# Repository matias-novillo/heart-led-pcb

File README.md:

# Heart LED Board

A heart-shaped PCB with 12 red LEDs around the edge. Press the button and the LEDs light up one after the other around the heart, then all of them light for a second at the end. Runs off a CR2032 coin cell and sleeps between presses.

Designed in KiCad, fabricated by JLCPCB, hand soldered.

## Status

- [x] Schematic
- [x] PCB layout (DRC, ERC and schematic parity clean)
- [x] Boards and parts ordered
- [ ] Assembly
- [ ] Firmware
- [ ] Tested

## Specs

| | |
|---|---|
| Board | 70 × 63 mm, 2-layer FR-4, 1.6 mm |
| MCU | STM32G031F6P6 (Cortex-M0+, TSSOP-20) |
| LEDs | 12 × red 1206 (LTST-C150KRKT), 220 Ω each, about 4.5 mA |
| Power | CR2032 coin cell, no regulator |
| Input | One tactile button on PC15 (internal pull-up, wakes the MCU) |
| Programming | 5-pin SWD header (3V3, SWDIO, SWCLK, NRST, GND) |

## How it works

Each LED has its own GPIO pin and resistor, so the MCU can light any LED directly. Only one LED is on at a time during the chase, which keeps the load on the coin cell to about 6.5 mA.

Lighting all 12 at once would pull about 54 mA, which a CR2032 can't supply without the voltage sagging and the MCU browning out. For the "all on" finale, the firmware multiplexes: it cycles through small groups of LEDs fast enough that they all look lit, while the battery only ever sees a few LEDs' worth of current.

Between presses the MCU sits in Stop mode at a few µA. The button wakes it through an EXTI interrupt.

## Pin map

| Signal | MCU pin | Pin # |
|---|---|---|
| LED1–LED8 | PA0–PA7 | 7–14 |
| LED9 | PA8/PB0/PB1/PB2 | 15 |
| LED10 | PA9/PA11 | 16 |
| LED11 | PA10/PA12 | 17 |
| LED12 | PB7/PB8 | 1 |
| Button | PC15 | 3 |
| SWDIO | PA13 | 18 |
| SWCLK | PA14 | 19 |
| NRST | PF2-NRST | 6 |

Pins 1, 15, 16 and 17 have several GPIOs bonded to one physical pin. Only one GPIO per pin should be configured as an output; the rest stay in analog mode.

## Repository layout

```
hardware/      KiCad project (schematic, PCB, project file)
fab/           Gerbers and drill files sent to JLCPCB
docs/          Schematic PDF and BOM
images/        Renders and photos
firmware/      STM32CubeIDE project (coming soon)
```

## Bill of materials

| Ref | Qty | Part | Manufacturer part # |
|---|---|---|---|
| U1 | 1 | STM32G031F6P6 | STM32G031F6P6 |
| D1–D12 | 12 | Red LED, 1206 | LTST-C150KRKT |
| R1–R12 | 12 | 220 Ω, 1206 | RC1206FR-07220RL |
| C1, C3 | 2 | 100 nF, 0805 | CL21B104KBCNNNC |
| C2 | 1 | 4.7 µF, 0805 | CL21A475KAQNNNE |
| SW1 | 1 | 6 mm tactile switch | B3F-1000 |
| BT1 | 1 | CR2032 holder | Keystone 3034 |
| J1 | 1 | 1×5 2.54 mm header | PRPC040SAAN-RC (cut to 5) |

## Programming

The board is flashed over SWD using the ST-Link built into a NUCLEO-G071RB. Remove the two CN4 jumpers on the Nucleo, then wire its CN11 header to J1:

| Nucleo CN11 | J1 |
|---|---|
| 1 VDD_TARGET | 1 3V3 |
| 2 SWCLK | 3 SWCLK |
| 3 GND | 5 GND |
| 4 SWDIO | 2 SWDIO |
| 5 NRST | 4 NRST (optional, needs SB19 opened on the Nucleo) |

The heart runs on its own coin cell while programming. VDD_TARGET only senses the target voltage.

## What I'd change in a rev 2

- More even LED spacing around the outline (the gaps currently range from about 7 mm to 19 mm; the firmware compensates by scaling the step delay to each gap)
- A ground pour on the back layer
- Decoupling caps closer to the VDD pin

## License

Hardware: [CERN-OHL-P v2](https://ohwr.org/cern_ohl_p_v2.txt)
Firmware: MIT

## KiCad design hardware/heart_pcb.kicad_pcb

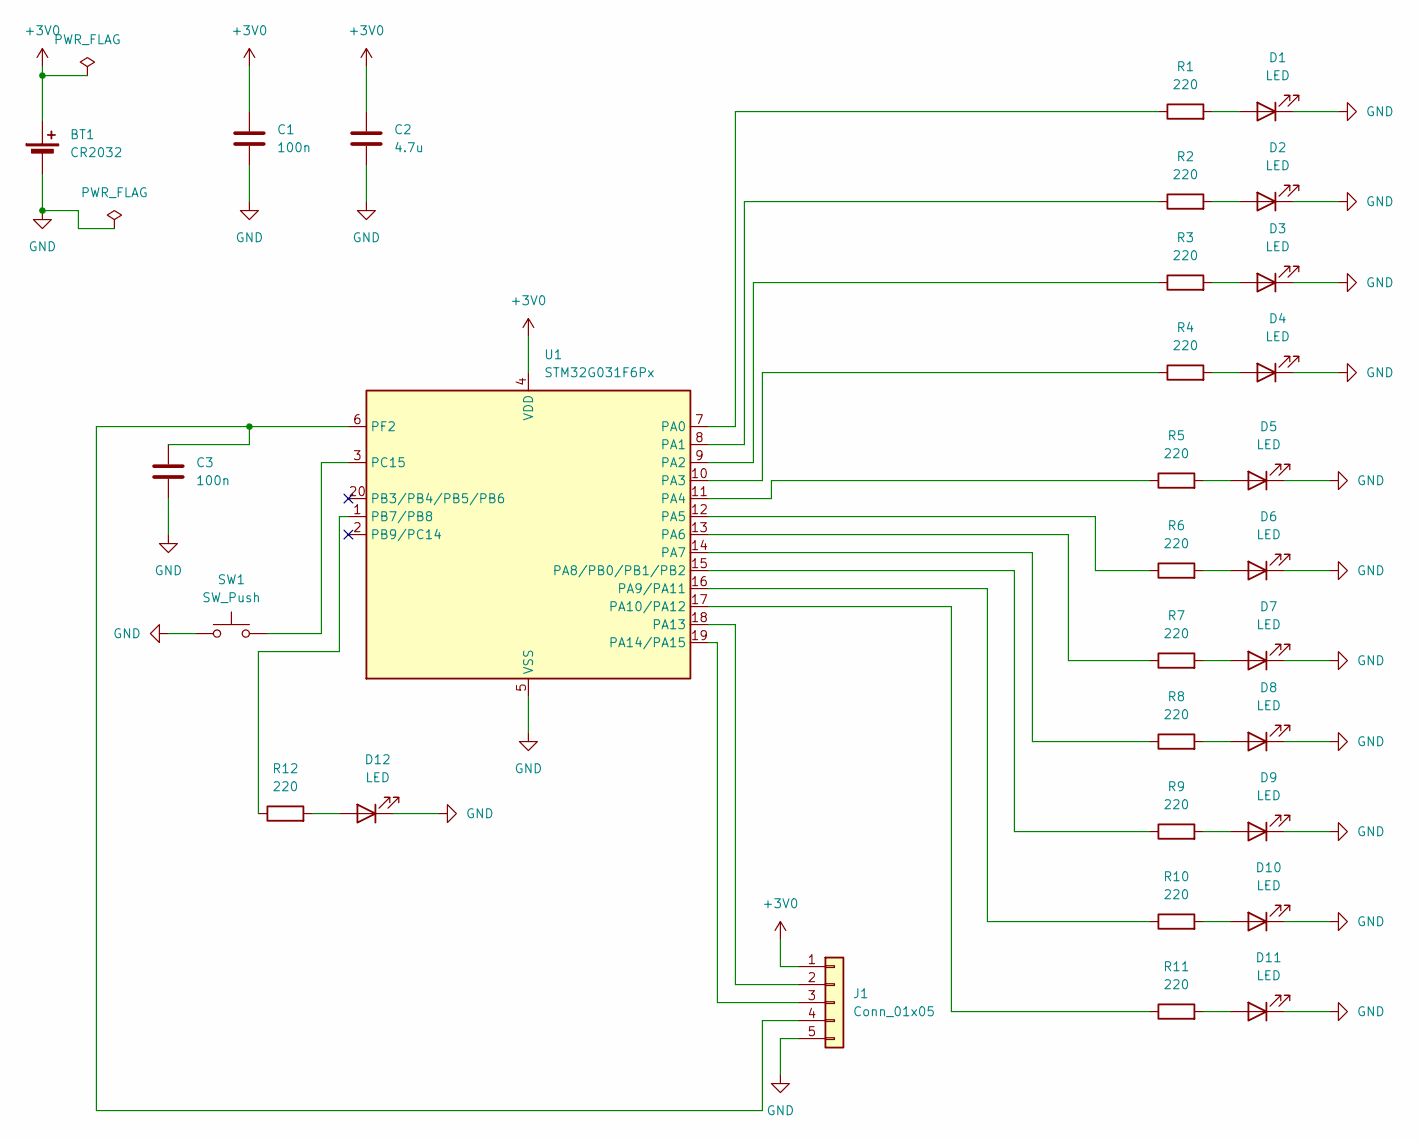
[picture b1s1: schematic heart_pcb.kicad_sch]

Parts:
BT1: CR2032; BatteryHolder_Keystone_3034_1x20mm
C1, C3: 100n; C_0805_2012Metric_Pad1.18x1.45mm_HandSolder
C2: 4.7u; C_0805_2012Metric_Pad1.18x1.45mm_HandSolder
D1, D2, D3, D4, D5, D6, D7, D8, D9, D10, D11, D12: LED; LED_1206_3216Metric_Pad1.42x1.75mm_HandSolder
J1: Conn_01x05; PinHeader_1x05_P2.54mm_Vertical
R1, R2, R3, R4, R5, R6, R7, R8, R9, R10, R11, R12: 220; R_1206_3216Metric_Pad1.30x1.75mm_HandSolder
SW1: SW_Push; SW_PUSH_6mm
U1: STM32G031F6Px; TSSOP-20_4.4x6.5mm_P0.65mm

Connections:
+3V0: BT1.1 (+), C1.1, C2.1, J1.1, U1.4 (VDD)
GND: BT1.2 (-), C1.2, C2.2, C3.2, D1.1 (K), D2.1 (K), D3.1 (K), D4.1 (K), D5.1 (K), D6.1 (K), D7.1 (K), D8.1 (K), D9.1 (K), D10.1 (K), D11.1 (K), D12.1 (K), J1.5, SW1.1, U1.5 (VSS)
unnamed: D1.2 (A), R1.2
unnamed: D2.2 (A), R2.2
unnamed: D3.2 (A), R3.2
unnamed: D4.2 (A), R4.2
unnamed: D5.2 (A), R5.2
unnamed: D6.2 (A), R6.2
unnamed: D7.2 (A), R7.2
unnamed: D8.2 (A), R8.2
unnamed: D9.2 (A), R9.2
unnamed: D10.2 (A), R10.2
unnamed: D11.2 (A), R11.2
unnamed: D12.2 (A), R12.2
unnamed: J1.2, U1.18 (PA13)
unnamed: J1.3, U1.19 (PA14/PA15)
unnamed: C3.1, J1.4, U1.6 (PF2)
unnamed: R1.1, U1.7 (PA0)
unnamed: R2.1, U1.8 (PA1)
unnamed: R3.1, U1.9 (PA2)
unnamed: R4.1, U1.10 (PA3)
unnamed: R5.1, U1.11 (PA4)
unnamed: R6.1, U1.12 (PA5)
unnamed: R7.1, U1.13 (PA6)
unnamed: R8.1, U1.14 (PA7)
unnamed: R9.1, U1.15 (PA8/PB0/PB1/PB2)
unnamed: R10.1, U1.16 (PA9/PA11)
unnamed: R11.1, U1.17 (PA10/PA12)
unnamed: R12.1, U1.1 (PB7/PB8)
unnamed: SW1.2, U1.3 (PC15)

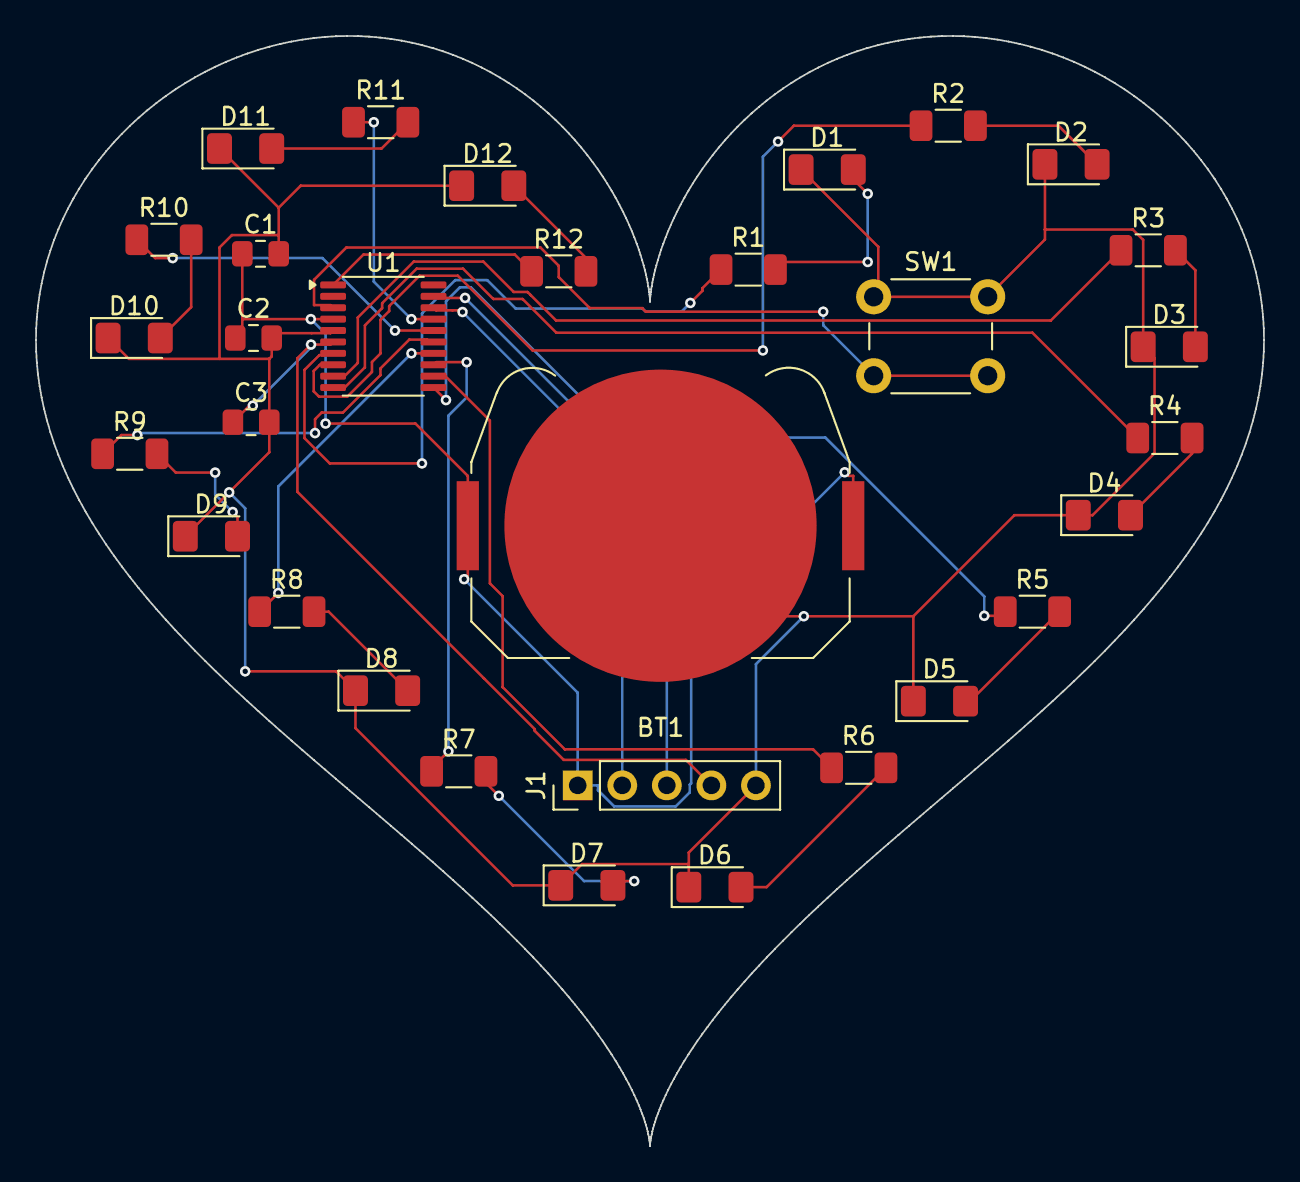
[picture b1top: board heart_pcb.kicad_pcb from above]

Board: 2 copper layers, 70.0 x 63.3 mm, 31 parts (0 on the bottom side), 30 nets.
